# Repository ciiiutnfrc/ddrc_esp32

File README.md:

# DDRC-ESP32: Controlador para robot de tracción diferencial basado en ESP32

DDRC-ESP32 (Differential Driver Robot Controller con ESP32) es una placa de control embebido para robots de tracción diferencial. 
El controlador diferencial está basado en el módulo [ESP32-WROOM-32E](https://www.espressif.com/sites/default/files/documentation/esp32-wroom-32e_esp32-wroom-32ue_datasheet_en.pdf) de la marca [Espressif](https://www.espressif.com/), el cual cuenta con un SoC (System On Chip) modelo [ESP32-D0WD-V3](https://www.espressif.com/sites/default/files/documentation/esp32_datasheet_en.pdf).
La elección de este módulo se debe principalmente a que está soportado por [micro-ROS](https://micro.ros.org/docs/overview/hardware/). 

El desarrollo del controlador diferencial se llevó a cabo como Proyecto Final de la carrera de Ingeniería Electrónica en la [Facultad Regional Córdoba](https://www.frc.utn.edu.ar/) de la Universidad Tecnológica Nacional.
El título del proyecto es _"Controlador Embebido para Robot de Tracción Differencial"_ y fue desarrollado por Gustavo Albarrán, Dante Ruiz y Juan Nicolodi bajo la dirección del Ing. Gonzalo Perez-Paina y del Ing. Diego Gonzalez Dondo.

Este controlador tiene por finalidad servir de base al desarrollo de robots de tracción diferencial cuyos algoritmos de navegación y control estén basados en [ROS 2](http://docs.ros.org/).

Las funciones principales del controlador diferencial son:
1. Leer la información de los codificadores ópticos acoplados a las ruedas de tracción.
1. Ajustar las velocidades de los motores de tracción mediante controladores PID.
1. Realizar el cálculo de la odometrı́a con la información de los codificadores ópticos acoplados a las ruedas.
1. Leer la tensión de la(s) batería(s) del robot.
1. Comunicarse con la PC a bordo del robot.

La siguiente imagen muestra un render del PCB del controlador diferencial.

## Videos

* [Proyecto Final: Controlador para robot de tracción diferencial compatible con ROS 2](https://www.youtube.com/watch?v=9FsznQ60jsQ&ab_channel=CIIIUTN-FRC)

## Documentación adicional

* [Ejemplo `blink` con ESP-IDF y Docker](doc/IDFBlinkDocker.md)
* [Nodo micro-ROS de ejemplo en ESP32 con Docker](doc/ESP32MicroROS.md).
* [Servidor HTTP para evaluación sobre un robot móvil](doc/HTTPServerDDR.md).

## Licencia
  <p xmlns:cc="http://creativecommons.org/ns#" xmlns:dct="http://purl.org/dc/terms/"><a property="dct:title" rel="cc:attributionURL" href="https://github.com/ciiiutnfrc/ddrc_esp32">DDRC-ESP32: Controlador para robot de tracción diferencial basado en ESP32</a> by <span property="cc:attributionName">Gustavo Albarran, Dante Ruiz, Juan Nicolodi, Diego Gonzalez Dondo, Gonzalo Perez Paina</span> is licensed under <a href="http://creativecommons.org/licenses/by-sa/4.0/?ref=chooser-v1" target="_blank" rel="license noopener noreferrer" style="display:inline-block;">CC BY-SA 4.0</a></p>

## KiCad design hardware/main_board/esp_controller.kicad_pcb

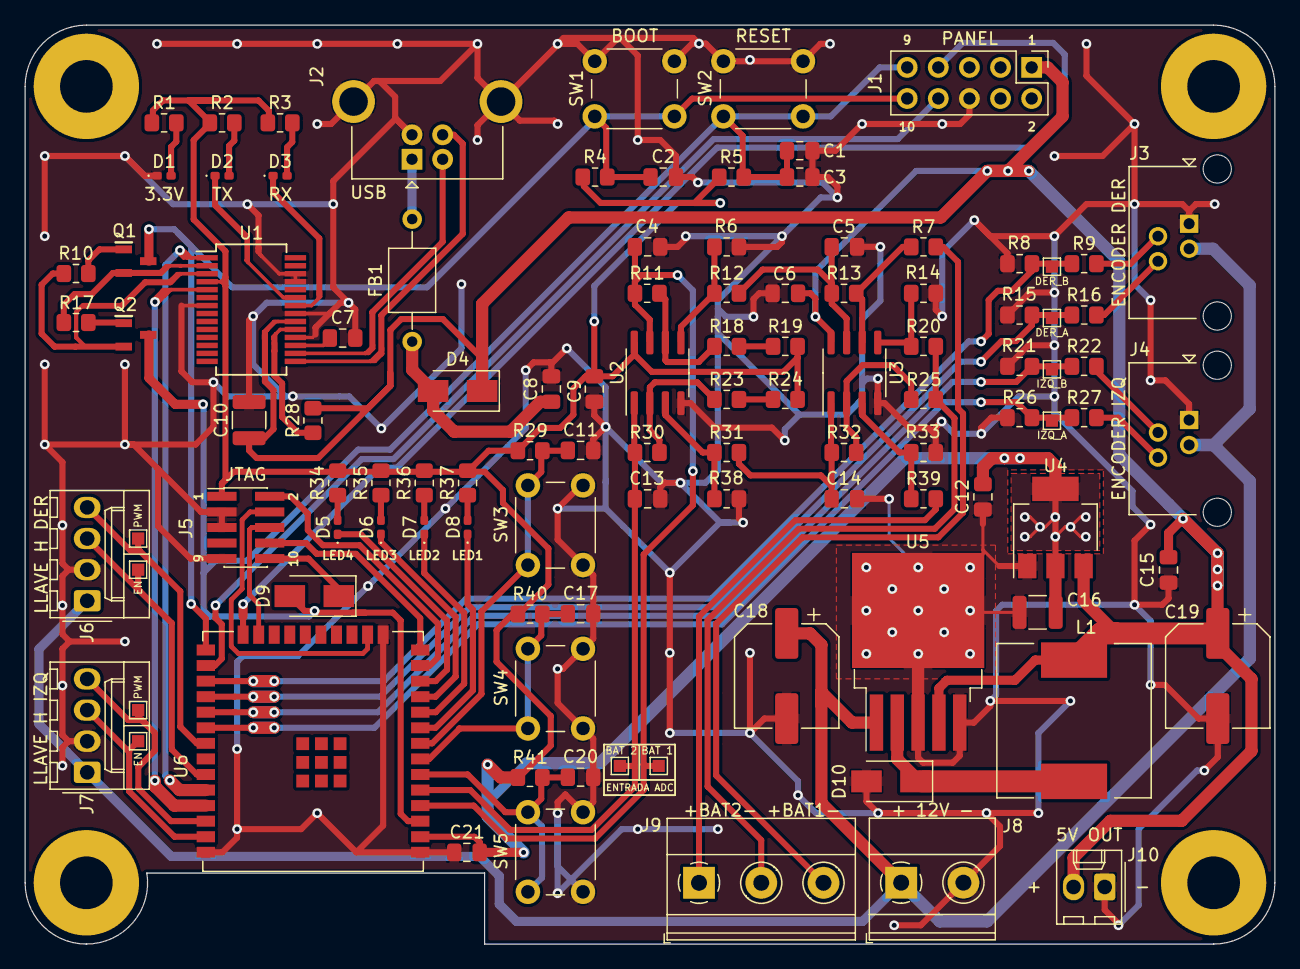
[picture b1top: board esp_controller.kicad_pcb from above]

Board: 2 copper layers, 102.0 x 75.0 mm, 111 parts (0 on the bottom side), 71 nets.

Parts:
C1, C2, C3, C4, C5, C6, C7, C9, C11, C13, C14, C15, C17, C20, C21: 100nF; C_0805_2012Metric_Pad1.18x1.45mm_HandSolder
C8: 10nF; C_0805_2012Metric_Pad1.18x1.45mm_HandSolder
C10: 4.7uF; C_1210_3225Metric
C12: 22uF; C_0805_2012Metric_Pad1.18x1.45mm_HandSolder
C16: 22uF; C_1210_3225Metric
C18: 680uF; CP_Elec_8x11.9
C19: 220uF; CP_Elec_8x11.9
D1, D2, D3, D5, D6, D7, D8: LED; LED_0402_1005Metric_Pad0.77x0.64mm_HandSolder
D4: SS34; D_SMA
D9: D; D_SMA
D10: 1N5824; D_SMA
FB1: Ferrite_Bead; L_Axial_L5.0mm_D3.6mm_P10.00mm_Horizontal_Murata_BL01RN1A2A2
H1, H2, H3, H4: MountingHole_4.3mm_M4_Pad
J1: Conn_02x05_Odd_Even; PinHeader_2x05_P2.54mm_Vertical
J2: USB_B; USB_B_OST_USB-B1HSxx_Horizontal
J3, J4: RJ14; RJ14_Connfly_DS1133-S4_Horizontal
J5: Conn_02x05_Odd_Even; PinHeader_2x05_P1.27mm_Vertical_SMD
J6, J7: Conn_01x04; Molex_KK-254_AE-6410-04A_1x04_P2.54mm_Vertical
J8: Conn_01x02; TerminalBlock_Phoenix_MKDS-1,5-2-5.08_1x02_P5.08mm_Horizont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
J9: Conn_01x03; TerminalBlock_Phoenix_MKDS-1,5-3-5.08_1x03_P5.08mm_Horizont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
J10: Conn_01x02; Molex_KK-254_AE-6410-02A_1x02_P2.54mm_Vertical
L1: 33uH; L_12x12mm_H8mm
Q1, Q2: MMS8050-H-TP; SOT96P237X122-3N
R1, R2, R3, R34, R35, R36, R37: 270; R_0805_2012Metric_Pad1.20x1.40mm_HandSolder
R4, R5, R6, R7, R8, R10, R15, R17, R20, R21, R25, R26, R29, R38, R39, R40, R41: 10k; R_0805_2012Metric_Pad1.20x1.40mm_HandSolder
R9, R16, R22, R27: 27k; R_0805_2012Metric_Pad1.20x1.40mm_HandSolder
R11, R28, R30: 1k; R_0805_2012Metric_Pad1.20x1.40mm_HandSolder
R12, R31: 2k; R_0805_2012Metric_Pad1.20x1.40mm_HandSolder
R13, R14, R18, R23, R32, R33: 2.2k; R_0805_2012Metric_Pad1.20x1.40mm_HandSolder
R19, R24: 300; R_0805_2012Metric_Pad1.20x1.40mm_HandSolder
SW1, SW2, SW3, SW4, SW5: SW_Push; SW_PUSH_6mm
TP1, TP2, TP3, TP4, TP5, TP6, TP7, TP8, TP9, TP10: TestPoint_Probe; TestPoint_Pad_1.0x1.0mm
U1: FT232RL; SSOP-28_5.3x10.2mm_P0.65mm
U2, U3: MCP6002-xSN; SOIC-8_3.9x4.9mm_P1.27mm
U4: AMS1117-3.3; SOT-223-3_TabPin2
U5: LM2596S-5; TO-263-5_TabPin3
U6: ESP32-WROOM-32E; ESP32-WROOM-32E-with-keep-area

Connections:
3V3: C9.1, C12.1, C16.1, C21.1, J5.1, R1.1, R2.1, R3.1, R4.1, R5.1, R19.2, R24.2, R29.1, R34.2, R35.2, R36.2, R37.2, R40.1, R41.1, U1.4, U2.8, U4.2, U6.2
5V: C6.1, C10.1, C15.1, C19.1, D4.1, J1.1, J10.2, L1.2, R28.1, U1.20, U3.8, U4.3, U5.4
12V: C18.1, J3.3, J4.3, J6.1, J7.1, J8.1, U5.1
BOOT: C2.1, J1.10, Q1.3, R4.2, SW1.2, U6.25
DTR: Q1.2, R17.2, U1.2
EN: C1.1, C3.1, D9.2, J1.9, Q2.3, R5.2, SW2.2, U6.3
ENC_DER_A: R15.1, R16.1, TP2.1, U6.28
ENC_DER_B: R8.1, R9.1, TP1.1, U6.27
ENC_IZQ_A: R26.1, R27.1, TP4.1, U6.30
ENC_IZQ_B: R21.1, R22.1, TP3.1, U6.29
EN_MOT_DER: J6.3, TP6.1, U6.33
EN_MOT_IZQ: J7.3, TP8.1, U6.37
GND: C1.2, C2.2, C3.2, C4.1, C5.1, C6.2, C7.2, C8.2, C9.2, C10.2, C11.2, C12.2, C13.1, C14.1, C15.2, C16.2, C17.2, C18.2, C19.2, C20.2, C21.2, D1.1, D10.2, J1.6, J2.4, J2.5, J3.1, J4.1, J5.3, J5.5, J5.9, J6.2, J7.2, J8.2, J10.1, R6.1, R8.2, R14.1, R15.2, R21.2, R26.2, R33.1, R38.1, SW1.1, SW2.1, SW3.1, SW4.1, SW5.1, U1.7, U1.18, U1.21, U1.25, U1.26, U2.4, U3.4, U4.1, U5.3, U5.5, U6.1, U6.15, U6.38
JTAG_TCK: J5.4, U6.16
JTAG_TDI: J5.8, U6.14
JTAG_TDO: J5.6, U6.23
JTAG_TMS: J5.2, U6.13
LED1: D8.1, U6.9
LED2: D7.1, U6.10
LED3: D6.1, U6.11
LED4: D5.1, U6.12
LED_EXT1: J1.7, U6.24
LED_EXT2: J1.8, U6.26
MED_BAT1: C4.2, R11.1, TP10.1, U2.7, U6.4
MED_BAT2: C13.2, R30.1, TP9.1, U2.1, U6.5
unnamed: C5.2, R12.2, R13.1, U3.7
unnamed: C7.1, U1.17
unnamed: C14.2, R31.2, R32.1, U3.1
unnamed: D1.2, R1.2
unnamed: D2.1, U1.23
unnamed: D2.2, R2.2
unnamed: D3.1, U1.22
unnamed: D3.2, R3.2
unnamed: D5.2, R34.1
unnamed: D6.2, R35.1
unnamed: D7.2, R36.1
unnamed: D8.2, R37.1
unnamed: D9.1, J5.10
unnamed: D10.1, L1.1, U5.2
unnamed: FB1.2, J2.1
unnamed: J3.2, R9.2
unnamed: J3.4, R16.2
unnamed: J4.2, R22.2
unnamed: J4.4, R27.2
unnamed: J9.1, R39.2
unnamed: J9.2, R20.2, R25.2
unnamed: J9.3, R7.2
unnamed: Q1.1, R10.1
unnamed: Q2.1, R17.1
unnamed: R11.2, R18.1, U2.6
unnamed: R6.2, R12.1, U2.5
unnamed: R7.1, R13.2, U3.6
unnamed: R14.2, R20.1, U3.5
unnamed: R18.2, R19.1
unnamed: R23.1, R30.2, U2.2
unnamed: R23.2, R24.1
unnamed: R25.1, R32.2, U3.2
unnamed: R28.2, U1.19
unnamed: R31.1, R38.2, U2.3
unnamed: R33.2, R39.1, U3.3
PUL1: C20.1, R41.2, SW5.2, U6.6
PUL2: C17.1, R40.2, SW4.2, U6.7
PUL3: C11.1, R29.2, SW3.2, U6.8
PWM_DER: J6.4, TP5.1, U6.31
PWM_IZQ: J7.4, TP7.1, U6.36
RTS: Q2.2, R10.2, U1.3
RXD0: U1.1, U6.34
TXD0: U1.5, U6.35
USB_D+: J2.3, U1.15
USB_D-: J2.2, U1.16
VBUS: C8.1, D4.2, FB1.1

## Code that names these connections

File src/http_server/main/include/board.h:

/******************************************************************************
 * Project: DDRC HTTP SERVER
 * File: board.h
 * Description: Board GPIO assigments
 * Created on: 05 jun. 2022
 * Last modified date: 20 Aug. 2022
 * Version: 0.0.1
 *
 * Este archivo complementa el Proyecto Final de grado de:
 * Albarran, Gustavo - Nicolodi, Juan - Ruiz, Dante
 * UNIVERSIDAD TECNOLOGICA NACIONAL - Fac. Reg. Cordoba
 *
 *	NOTE: 
 *
 ******************************************************************************/

#define BOARD DDRC_ESP32

#define BOOT_BUTTON    0

/* Define GPIO */
/* LEDs */
#define LED1    33
#define LED2    25
#define LED3    26
#define LED4    27

/* LEDs Externos */
#define LED_EXT1    2
#define LED_EXT2    4

#define GPIO_OUTPUT_LEDS ((1ULL<<LED1) | (1ULL<<LED2) | (1ULL<<LED3) | (1ULL<<LED4))
#define GPIO_OUTPUT_LEDS_EXT ((1ULL<<LED_EXT1) | (1ULL<<LED_EXT2) ) 
#define GPIO_OUTPUT_PIN_SEL  (GPIO_OUTPUT_LEDS | GPIO_OUTPUT_LEDS_EXT)

/* PULSADORES */
#define PUL1    34
#define PUL2    35
#define PUL3    32

#define GPIO_INPUT_PIN_SEL  ((1ULL<<PUL1) | (1ULL<<PUL2) | (1ULL<<PUL3))


/* ENCODERS */
#define ENC_IZQ_A   18
#define ENC_IZQ_B   5
#define ENC_DER_A   17
#define ENC_DER_B   16

/* PWM MOTORES */
#define PWM_IZQ     22
#define PWM_DER     19

/* Habilitacion MOTORES */
#define EN_MOT_IZQ  23
#define EN_MOT_DER  21

#define ENABLE_MOTOR_MASK  ((1ULL<<EN_MOT_IZQ) | (1ULL<<EN_MOT_DER))

/* Ruedas */
#define RUEDA_IZQ      0
#define RUEDA_DER      1

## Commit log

2023-03-17 Add .gitignore for kicad files
2023-03-17 Add kicad files of ddrc-esp32 board
2023-03-17 Add kicad_lib folder and moves files
2023-03-29 Add documentation
2023-03-31 Update documentation
2023-03-31 Add http server example program
2023-04-25 Update README.md
    Agrega licencia CC
